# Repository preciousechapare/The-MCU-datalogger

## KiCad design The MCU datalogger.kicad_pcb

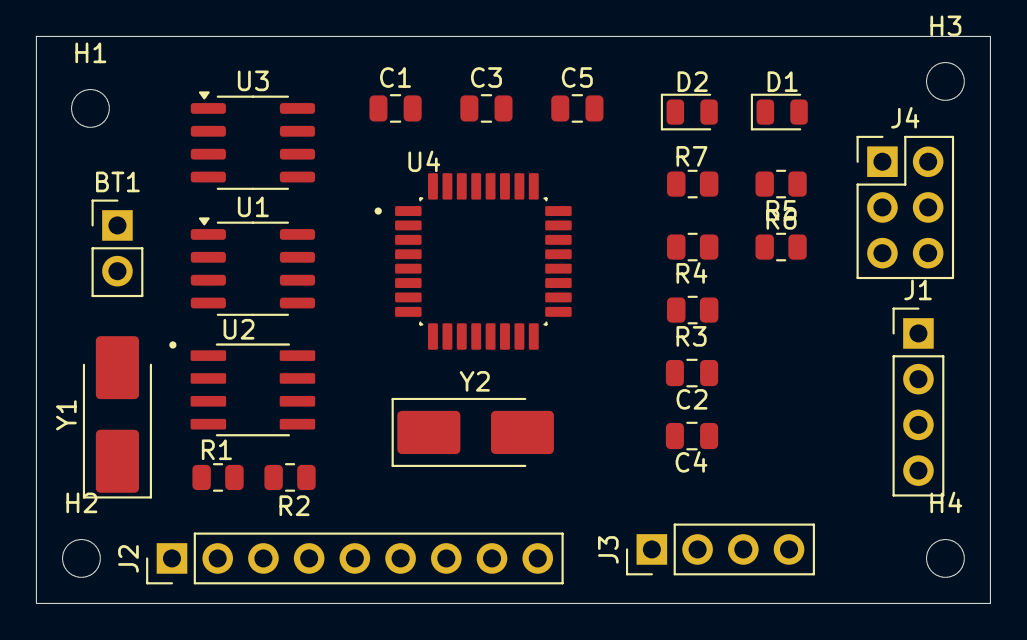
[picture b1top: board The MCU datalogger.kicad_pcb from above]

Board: 2 copper layers, 53.0 x 31.5 mm, 29 parts (0 on the bottom side), 26 nets, no tracks yet.

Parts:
BT1: Battery; PinHeader_1x02_P2.54mm_Vertical
C1, C4: 0.1uF; C_0805_2012Metric
C2, C3: 22pF; C_0805_2012Metric
C5: 100nF; C_0805_2012Metric
D1, D2: LED; LED_0805_2012Metric
H1, H2, H3, H4: MountingHole; MountingHole_2.1mm
J1, J3: Conn_01x04_Male; PinHeader_1x04_P2.54mm_Vertical
J2: Conn_01x09_Male; PinHeader_1x09_P2.54mm_Vertical
J4: Conn_02x03_Odd_Even; PinHeader_2x03_P2.54mm_Vertical
R1, R2, R6: 10K; R_0805_2012Metric
R3, R4: 4.7K; R_0805_2012Metric
R5, R7: 330; R_0805_2012Metric
U1, U3: 24LC1025; SOIC-8_3.9x4.9mm_P1.27mm
U2: DS1337S+; SOIC127P600X175-8N
U4: ATMEGA328P-AU; QFP80P900X900X120-32N
Y1: 32.768 KHz; Crystal_SMD_5032-2Pin_5.0x3.2mm_HandSoldering
Y2: 16 MHz; Crystal_SMD_5032-2Pin_5.0x3.2mm_HandSoldering

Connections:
D2: J2.1, U4.32 (PD2)
D3: J2.2, U4.1 (PD3)
D4: J2.3, U4.2 (PD4)
D5: J2.4, U4.9 (PD5)
D6: J2.5, U4.10 (PD6)
D7: J2.6, U4.11 (PD7)
D8: J2.7, U4.12 (PB0)
GND: BT1.2 (-), C1.2, C2.2, C3.2, C4.1, C5.2, J1.1, J2.8, J3.1, J4.6, R5.1, R7.2, U1.4 (GND), U1.7 (WP), U2.4 (GND), U3.3 (A2), U3.4 (GND), U3.7 (WP), U4.3 (GND), U4.5 (GND), U4.21 (GND)
MISO: J4.1, U4.16 (PB4)
MOSI: J4.4, U4.15 (PB3)
unnamed: BT1.1 (+), C5.1, D2.2 (A), U4.4 (VCC), U4.18 (AVCC)
unnamed: D1.1 (K), R5.2
unnamed: D2.1 (K), R7.1
unnamed: R2.2, U2.7 (SQW/~INT)
unnamed: U2.1 (X1), Y1.2
unnamed: U2.2 (X2), Y1.1
unnamed: R1.2, U2.3 (~INTA)
unnamed: C4.2, U4.20 (AREF)
unnamed: C2.1, U4.7 (PB6), Y2.2
unnamed: C3.1, U4.8 (PB7), Y2.1
RESET: J4.5, R6.2, U4.29 (PC6/~RESET)
RX: J3.3, U4.30 (PD0)
SCK: D1.2 (A), J1.4, J4.3, R3.2, U2.6 (SCL), U3.6 (SCL), U4.17 (PB5), U4.28 (PC5)
SDA: J1.3, R4.2, U1.5 (SDA), U2.5 (SDA), U3.5 (SDA), U4.27 (PC4)
TX: J3.4, U4.31 (PD1)
Vcc: C1.1, J1.2, J2.9, J3.2, J4.2, R1.1, R2.1, R3.1, R4.1, R6.1, U1.1 (A0), U1.2 (A1), U1.3 (A2), U1.8 (VCC), U2.8 (VCC), U3.1 (A0), U3.2 (A1), U3.8 (VCC)

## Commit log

2025-10-04 Initial commit of The MCU datalogger project files
2025-10-04 Initial commit of MCU datalogger project
2025-10-04 Add .gitignore file
2025-10-04 Initial commit before syncing with GitHub
2025-10-04 Have added required symbols to the schematic sheets.
2025-10-04 Added component values.
2025-10-04 Completed symbol-footprint associations.
2025-10-04 Completed wiring of main sheet.
2025-10-05 Initial commit - The MCU datalogger
2025-10-06 Setup Pcbnew - imported footprints and updated layout
2025-10-06 Completed placement of footprints.
